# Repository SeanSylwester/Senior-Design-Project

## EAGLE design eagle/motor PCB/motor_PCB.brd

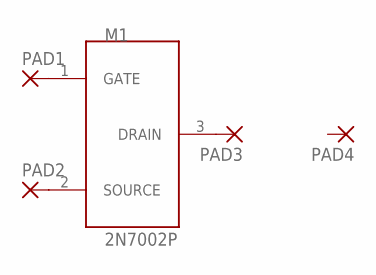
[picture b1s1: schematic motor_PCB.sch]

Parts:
M1: 2N7002P; TO-236AB
PAD1, PAD2, PAD3, PAD4: SMD2; SMD1,27-2,54

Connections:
unnamed: M1.1 (GATE), PAD1.1
unnamed: M1.2 (SOURCE), PAD2.1
unnamed: M1.3 (DRAIN), PAD3.1

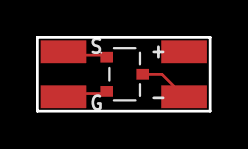
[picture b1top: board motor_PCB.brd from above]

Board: 2 copper layers, 9.6 x 4.1 mm, 5 parts (0 on the bottom side), 3 nets.

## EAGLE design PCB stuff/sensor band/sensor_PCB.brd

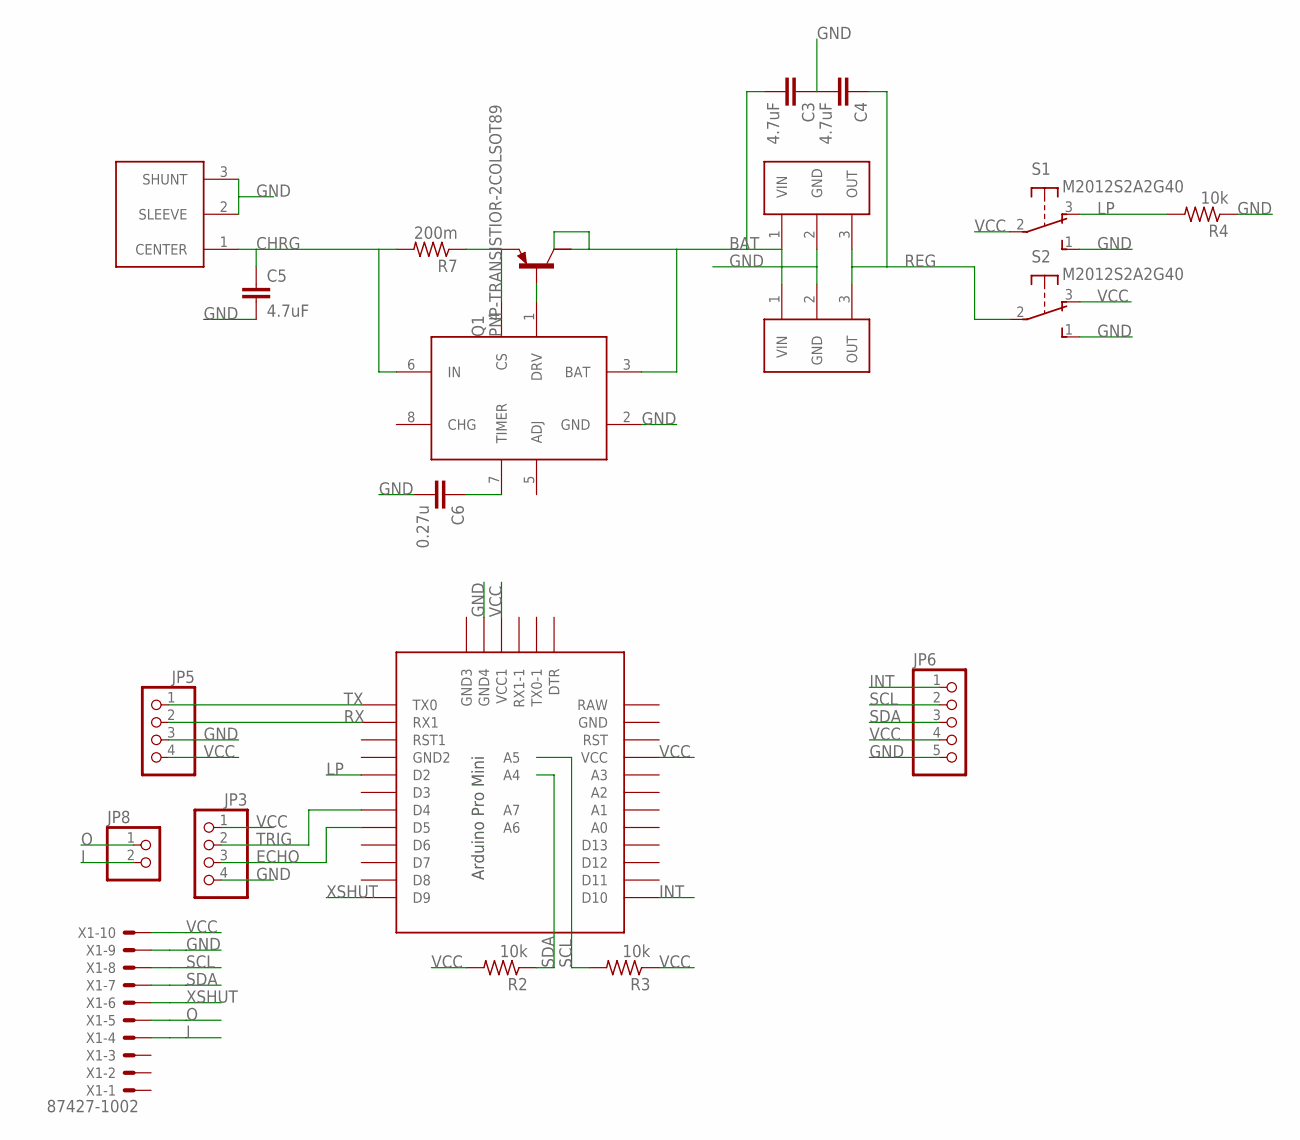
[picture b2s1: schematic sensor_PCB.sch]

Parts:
C3, C4, C5: 4.7uF; 0603
C6: 0.27u; 0805
JP3, JP5: PINHD-1X4; 1X04
JP6: PINHD-1X5; 1X05
JP8: PINHD-1X2; 1X02
Q1: PNP-TRANSISTIOR-2COLSOT89; SOT89
R2, R3, R4: 10k; R0603
R7: 200m; R0603
S1, S2: M2012S2A2G40
U$1: PRO-MINI-2
U$3: ADP2291; 8-MSOP
V3, V4: UCC283T-3; TO220V
V5: L712RAS
X1: 87427-1002

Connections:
BAT: C3.2, Q1.2 (C), Q1.2@1 (C/), U$3.3 (BAT), V3.1 (VIN), V4.1 (VIN)
CHRG: C5.1, R7.2, U$3.6 (IN), V5.1 (CENTER)
CS: Q1.3 (E), R7.1, U$3.4 (CS)
DRV: Q1.1 (B), U$3.1 (DRV)
ECHO: JP3.3, U$1.D5
GND: C3.1, C4.2, C5.2, C6.2, JP3.4, JP5.3, JP6.5, R4.1, S1.1 (S), S2.1 (S), U$1.GND3 (GND4), U$3.2 (GND), V3.2 (GND), V4.2 (GND), V5.2 (SLEEVE), V5.3 (SHUNT), X1.9
I: JP8.2, X1.4
INT: JP6.1, U$1.D10
LP: R4.2, S1.3 (O), U$1.D2
O: JP8.1, X1.5
REG: C4.1, S2.2, V3.3 (OUT), V4.3 (OUT)
RX: JP5.2, U$1.RX1
SCL: JP6.2, R3.2, U$1.A5, X1.8
SDA: JP6.3, R2.1, U$1.A4, X1.7
TIMER: C6.1, U$3.7 (TIMER)
TRIG: JP3.2, U$1.D4
TX: JP5.1, U$1.TX0
VCC: JP3.1, JP5.4, JP6.4, R2.2, R3.1, S1.2, S2.3 (O), U$1.VCC, U$1.VCC1, X1.10
XSHUT: U$1.D9, X1.6

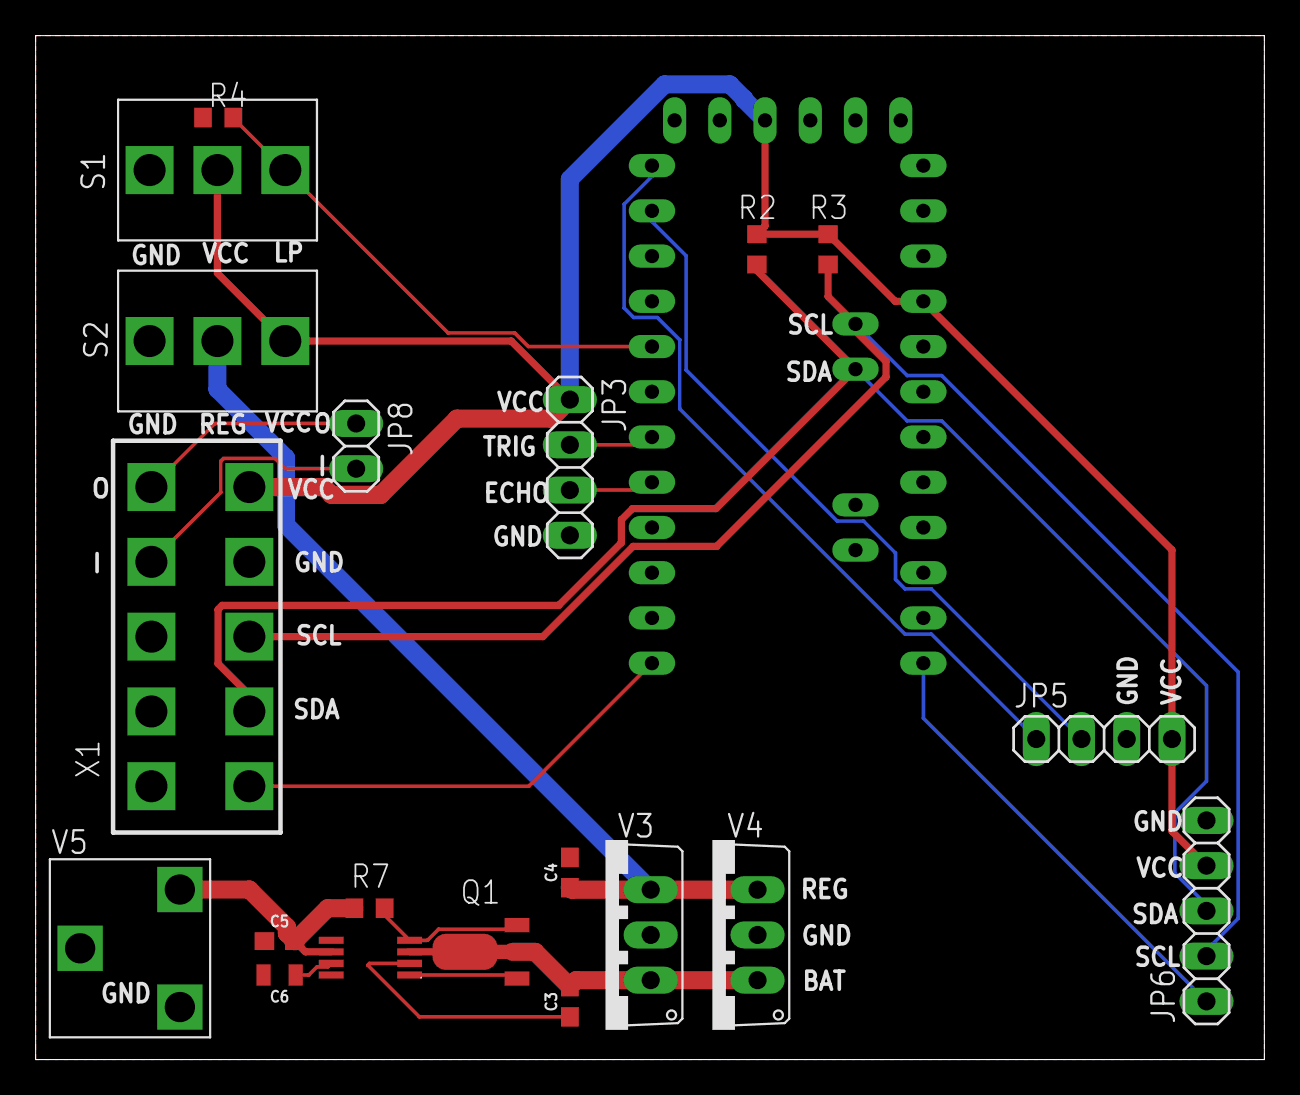
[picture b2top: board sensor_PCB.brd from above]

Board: 2 copper layers, 69.0 x 57.5 mm, 21 parts (0 on the bottom side), 19 nets.

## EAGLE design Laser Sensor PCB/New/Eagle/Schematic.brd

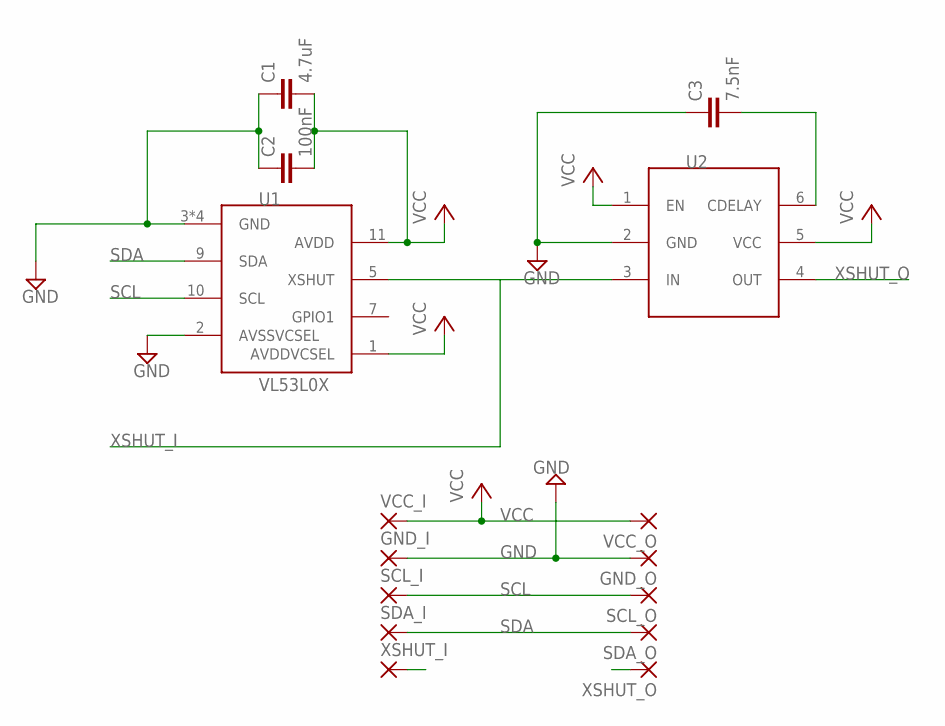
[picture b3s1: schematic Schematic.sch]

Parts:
C1: 4.7uF; 0603
C2: 100nF; 0603
C3: 7.5nF; 0402
GND_I: SMD2; SMD1,27-2,54
GND_O: SMD2; SMD1,27-2,54
SCL_I: SMD2; SMD1,27-2,54
SCL_O: SMD2; SMD1,27-2,54
SDA_I: SMD2; SMD1,27-2,54
SDA_O: SMD2; SMD1,27-2,54
U1: VL53L0X; OPTICAL_LGA12
U2: MAX6895AAZT+T; 6-THIN-SOT23
VCC_I: SMD2; SMD1,27-2,54
VCC_O: SMD2; SMD1,27-2,54
XSHUT_I: SMD2; SMD1,27-2,54
XSHUT_O: SMD2; SMD1,27-2,54

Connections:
CDELAY: C3.2, U2.6 (CDELAY)
GND: C1.1, C2.1, C3.1, GND_I.1, GND_O.1, U1.2 (AVSSVCSEL), U1.3 (GND), U1.4 (GND), U1.6 (GND), U1.12 (GND), U2.2 (GND)
SCL: SCL_I.1, SCL_O.1, U1.10 (SCL)
SDA: SDA_I.1, SDA_O.1, U1.9 (SDA)
VCC: C1.2, C2.2, U1.1 (AVDDVCSEL), U1.11 (AVDD), U2.1 (EN), U2.5 (VCC), VCC_I.1, VCC_O.1
XSHUT_I: U1.5 (XSHUT), U2.3 (IN), XSHUT_I.1
XSHUT_O: U2.4 (OUT), XSHUT_O.1

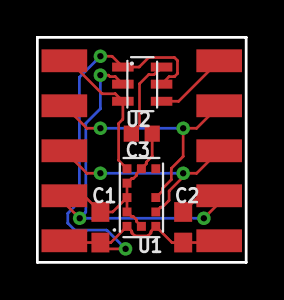
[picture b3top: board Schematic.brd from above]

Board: 2 copper layers, 11.6 x 12.5 mm, 15 parts (0 on the bottom side), 7 nets.

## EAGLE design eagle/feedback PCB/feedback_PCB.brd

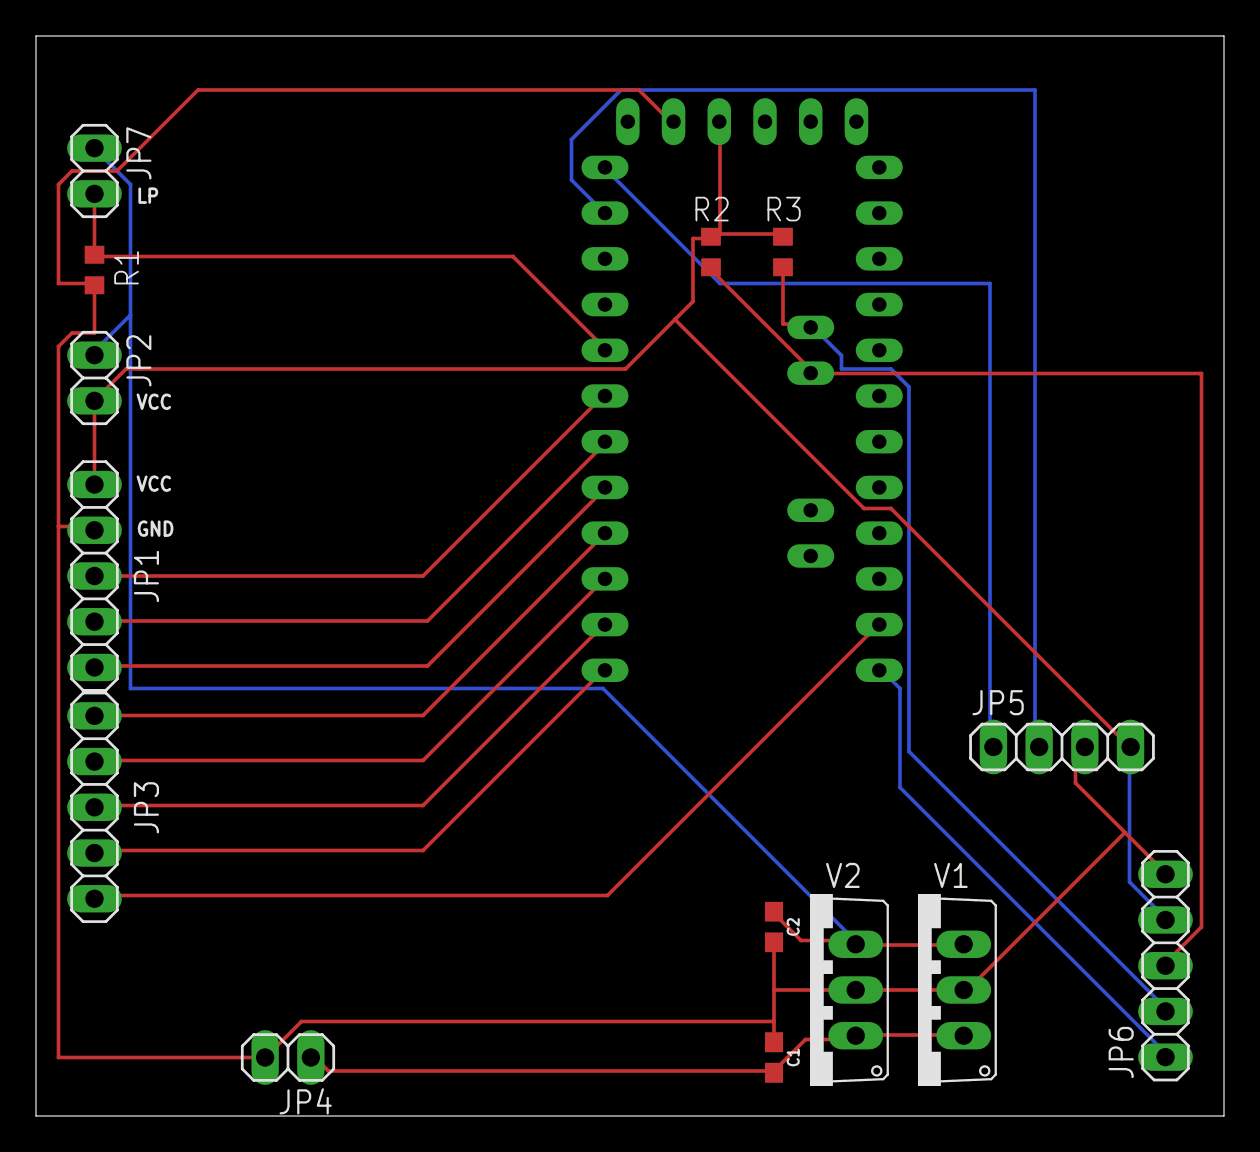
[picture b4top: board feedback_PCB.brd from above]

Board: 2 copper layers, 66.0 x 60.0 mm, 15 parts (0 on the bottom side), 18 nets.

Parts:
C1, C2: 4.7uF; 0603
JP1, JP3, JP6: 1X05
JP2, JP4, JP7: 1X02
JP5: 1X04
R1, R2, R3: 10k; R0603
U$1: PRO-MINI-2
V1, V2: UCC283T-3; TO220V

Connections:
BAT: C1.2, JP4.1, V1.1, V2.1
GND: C1.1, C2.2, JP1.4, JP4.2, JP5.3, JP6.5, R1.1, U$1.GND3, V1.2, V2.2
INT: JP6.1, U$1.D10
LP: JP7.2, R1.2, U$1.D2
unnamed: JP3.1, U$1.D11
unnamed: JP3.2, U$1.D9
unnamed: JP3.3, U$1.D8
unnamed: JP3.4, U$1.D7
unnamed: JP3.5, U$1.D6
unnamed: JP1.1, U$1.D5
unnamed: JP1.2, U$1.D4
unnamed: JP1.3, U$1.D3
REG: C2.1, JP2.1, JP7.1, V1.3, V2.3
RX: JP5.2, U$1.RX1
SCL: JP6.2, R3.2, U$1.A5
SDA: JP6.3, R2.1, U$1.A4
TX: JP5.1, U$1.TX0
VCC: JP1.5, JP2.2, JP5.4, JP6.4, R2.2, R3.1, U$1.VCC1

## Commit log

2020-01-28 removed unnecessary files
2020-01-28 organized PCB files

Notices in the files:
parts and their libraries:
SparkFun-Capacitors: Licensing: Creative Commons ShareAlike 4.0 International - https://creativecommons.org/licenses/by-sa/4.0
